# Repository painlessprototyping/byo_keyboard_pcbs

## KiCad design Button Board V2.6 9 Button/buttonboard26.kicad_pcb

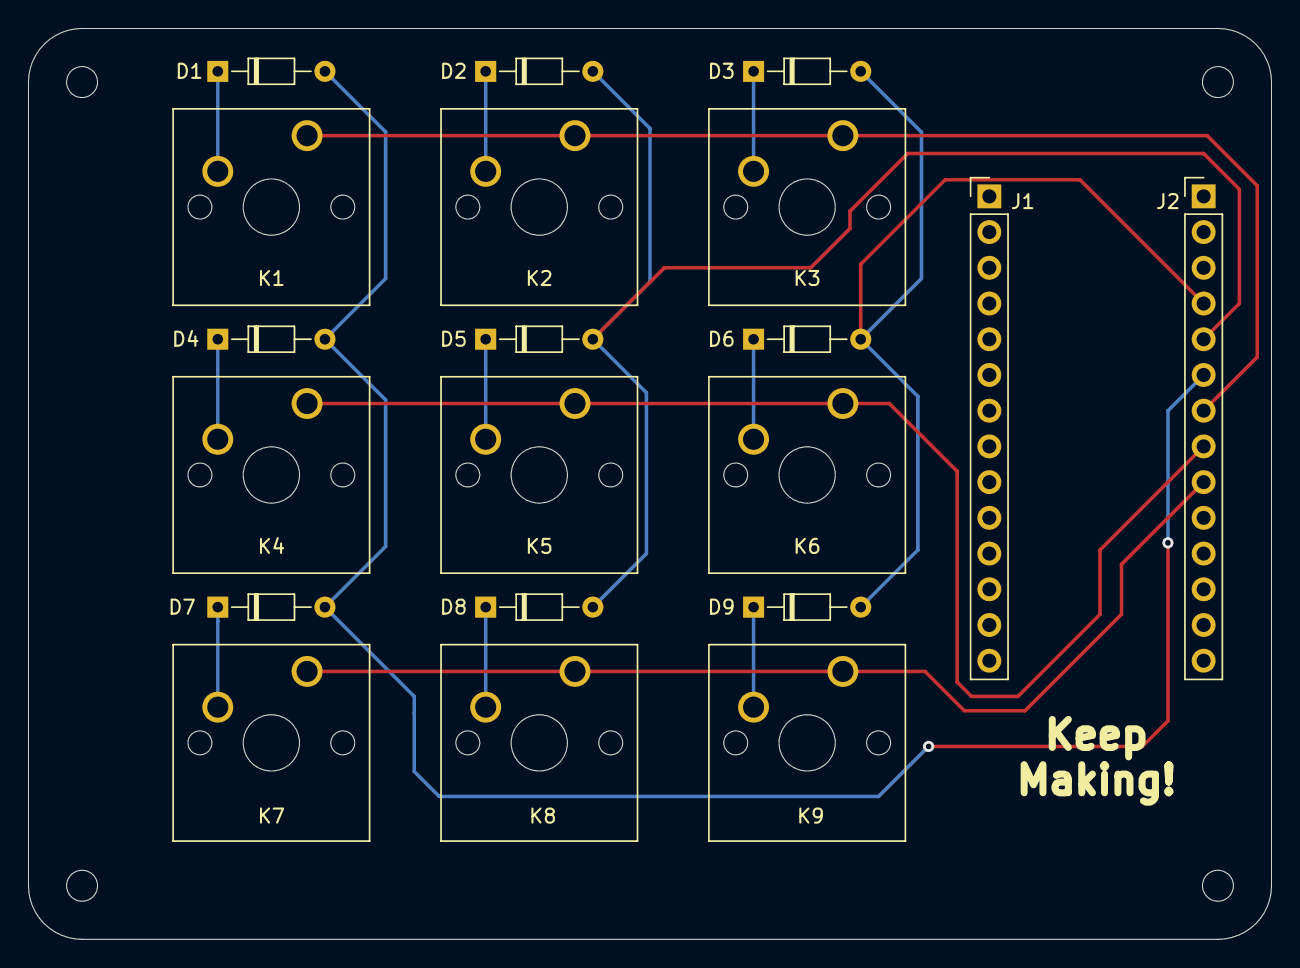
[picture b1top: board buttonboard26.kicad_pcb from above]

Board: 2 copper layers, 88.4 x 64.8 mm, 20 parts (0 on the bottom side), 15 nets.

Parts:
D1, D2, D3, D4, D5, D6, D7, D8, D9: DIODE; D_DO-34_SOD68_P7.62mm_Horizontal
J1, J2: Conn_01x14_Female; PinHeader_1x14_P2.54mm_Vertical
K1, K2, K3, K4, K5, K6, K7, K8, K9: KEYSW; SW_Cherry_MX_1.00u_PCB

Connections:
unnamed: D1.1, K1.2
unnamed: D1.2, D4.2, D7.2, J2.6
unnamed: D2.1, K2.2
unnamed: D2.2, D5.2, D8.2, J2.5
unnamed: D3.1, K3.2
unnamed: D3.2, D6.2, D9.2, J2.4
unnamed: D4.1, K4.2
unnamed: D5.1, K5.2
unnamed: D6.1, K6.2
unnamed: D7.1, K7.2
unnamed: D8.1, K8.2
unnamed: D9.1, K9.2
unnamed: J2.7, K1.1, K2.1, K3.1
unnamed: J2.8, K4.1, K5.1, K6.1
unnamed: J2.9, K7.1, K8.1, K9.1
